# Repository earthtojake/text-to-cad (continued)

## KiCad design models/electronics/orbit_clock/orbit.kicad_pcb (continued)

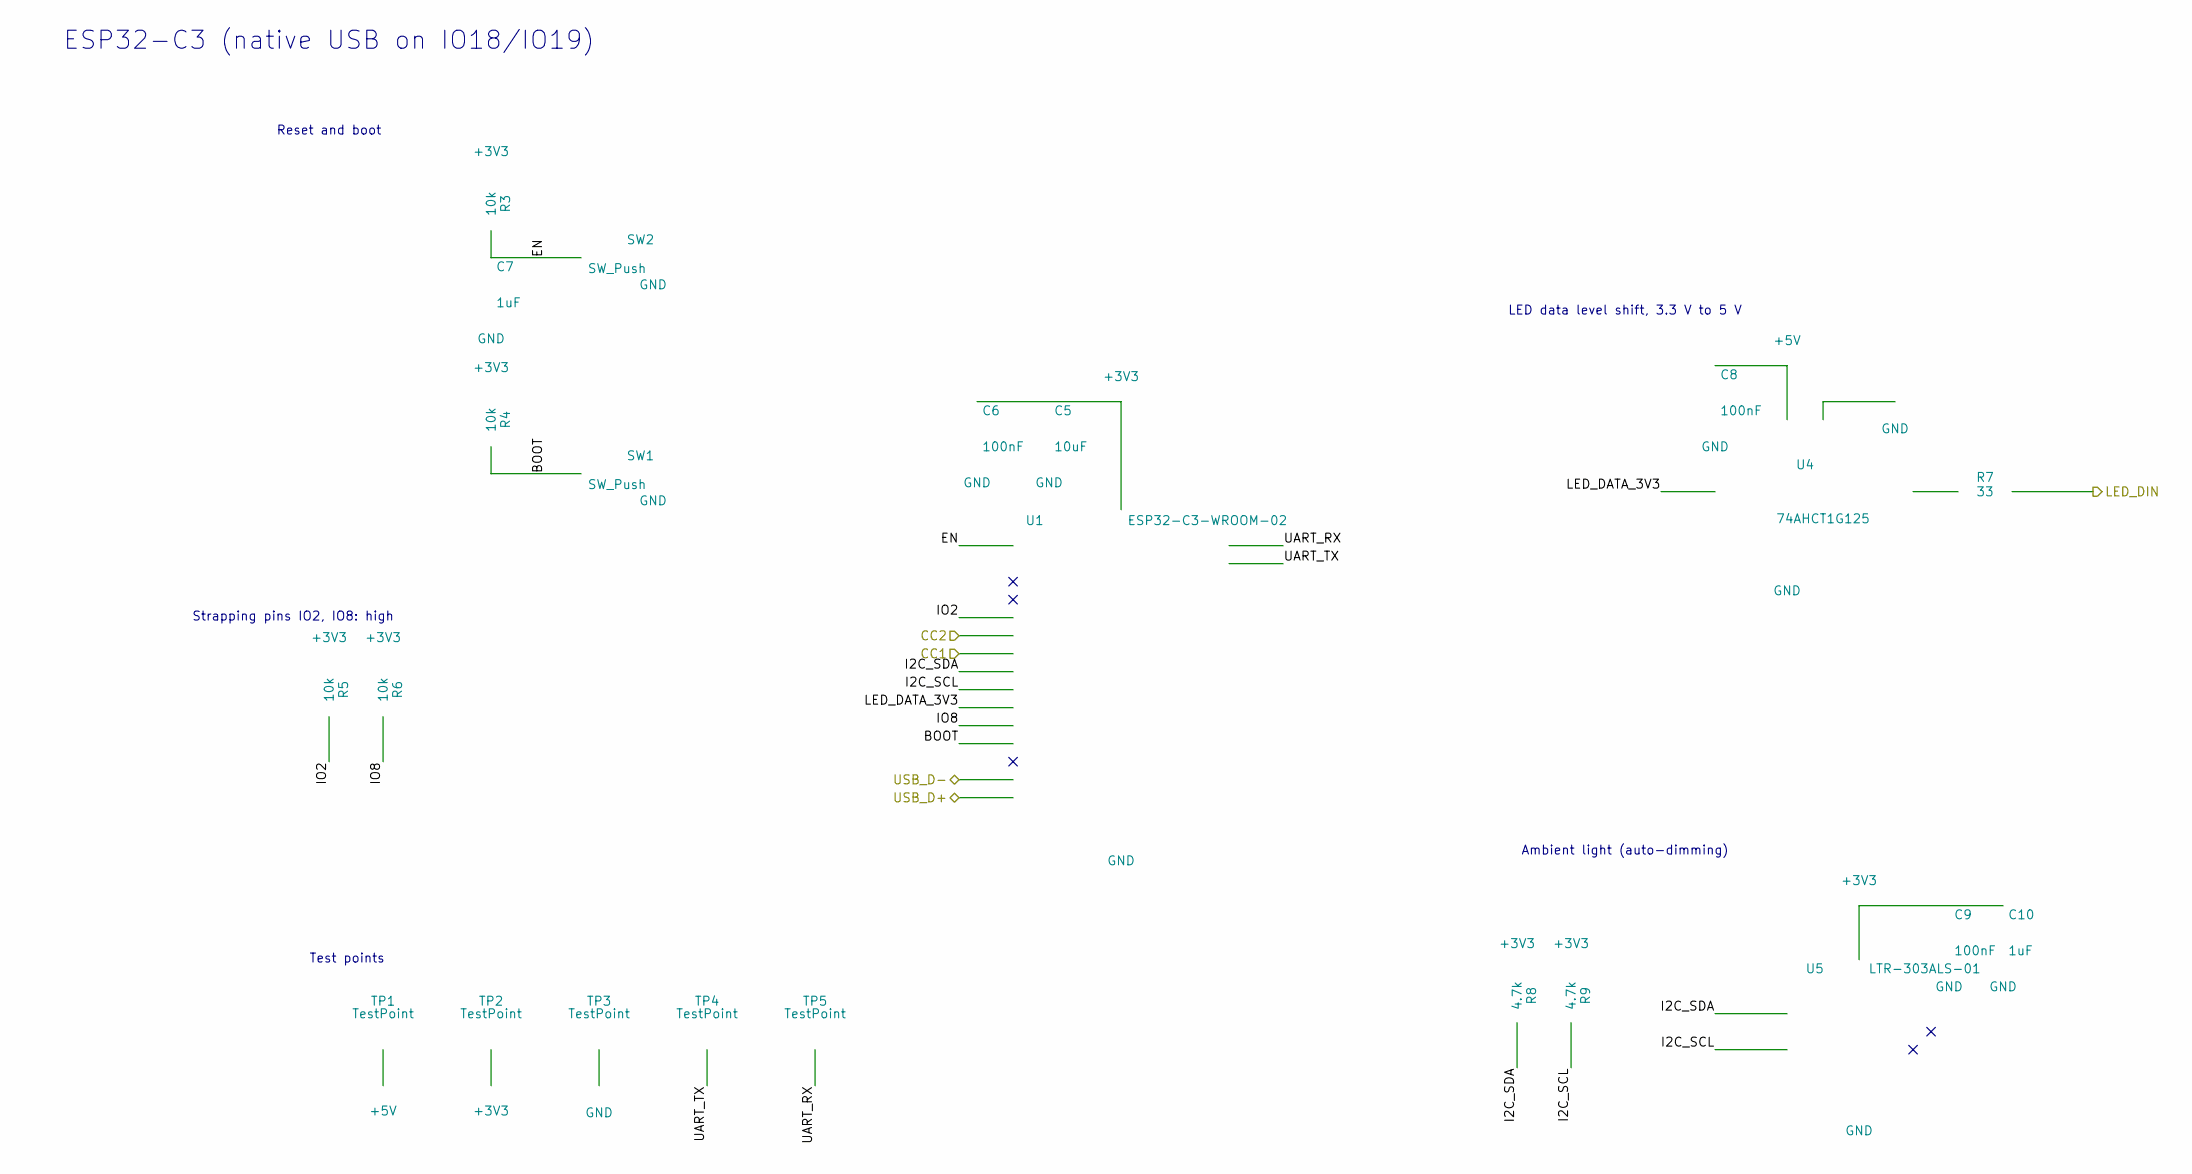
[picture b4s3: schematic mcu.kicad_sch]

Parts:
C5: 10uF; C_0805_2012Metric; MPN CL21A106KAYNNNE
C6, C8, C9: 100nF; C_0603_1608Metric; MPN CL10B104KB8NNNC
C7, C10: 1uF; C_0603_1608Metric; MPN CL10A105KB8NNNC
R3, R4, R5, R6: 10k; R_0603_1608Metric; MPN RC0603FR-0710KL
R7: 33; R_0603_1608Metric; MPN RC0603FR-0733RL
R8, R9: 4.7k; R_0603_1608Metric; MPN RC0603FR-074K7L
SW1, SW2: SW_Push; SW_SPST_TL3342; MPN TL3342F160QG
TP1, TP2, TP3, TP4, TP5: TestPoint; TestPoint_Pad_D1.5mm
U1: ESP32-C3-WROOM-02; MPN ESP32-C3-WROOM-02-N4
U4: 74AHCT1G125; SOT-23-5; MPN SN74AHCT1G125DBVR
U5: LTR-303ALS-01; Lite-On_LTR-303ALS-01; MPN LTR-303ALS-01

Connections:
+3V3: C5.1, C6.1, C9.1, C10.1, R3.1, R4.1, R5.1, R6.1, R8.1, R9.1, TP2.1 (1_1), U1.1 (3V3), U5.1 (VDD); also elsewhere on the board
+5V: C8.1, TP1.1 (1_1), U4.5 (VCC); also elsewhere on the board
/MCU/BOOT: R4.2, SW1.1, U1.8 (IO9)
/MCU/CC1: U1.3 (IO4); also elsewhere on the board
/MCU/CC2: U1.15 (IO3); also elsewhere on the board
/MCU/EN: C7.1, R3.2, SW2.1, U1.2 (EN)
/MCU/I2C_SCL: R9.2, U1.5 (IO6), U5.4 (SCL)
/MCU/I2C_SDA: R8.2, U1.4 (IO5), U5.6 (SDA)
/MCU/IO2: R5.2, U1.16 (IO2)
/MCU/IO8: R6.2, U1.7 (IO8)
/MCU/LED_DATA_3V3: U1.6 (IO7), U4.2
/MCU/LED_DIN: R7.2; also elsewhere on the board
/MCU/UART_RX: TP5.1 (1_1), U1.11 (IO20/RXD)
/MCU/UART_TX: TP4.1 (1_1), U1.12 (IO21/TXD)
/Power/USB_D+: U1.14 (IO19); also elsewhere on the board
/Power/USB_D-: U1.13 (IO18); also elsewhere on the board
GND: C5.2, C6.2, C7.2, C8.2, C9.2, C10.2, SW1.2, SW2.2, TP3.1 (1_1), U1.9 (GND), U1.19 (GND), U4.1, U4.3 (GND), U5.3 (GND); also elsewhere on the board
unnamed: R7.1, U4.4

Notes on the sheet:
ESP32-C3 (native USB on IO18/IO19)
Ambient light (auto-dimming)
LED data level shift, 3.3 V to 5 V
Strapping pins IO2, IO8: high
Reset and boot
Test points

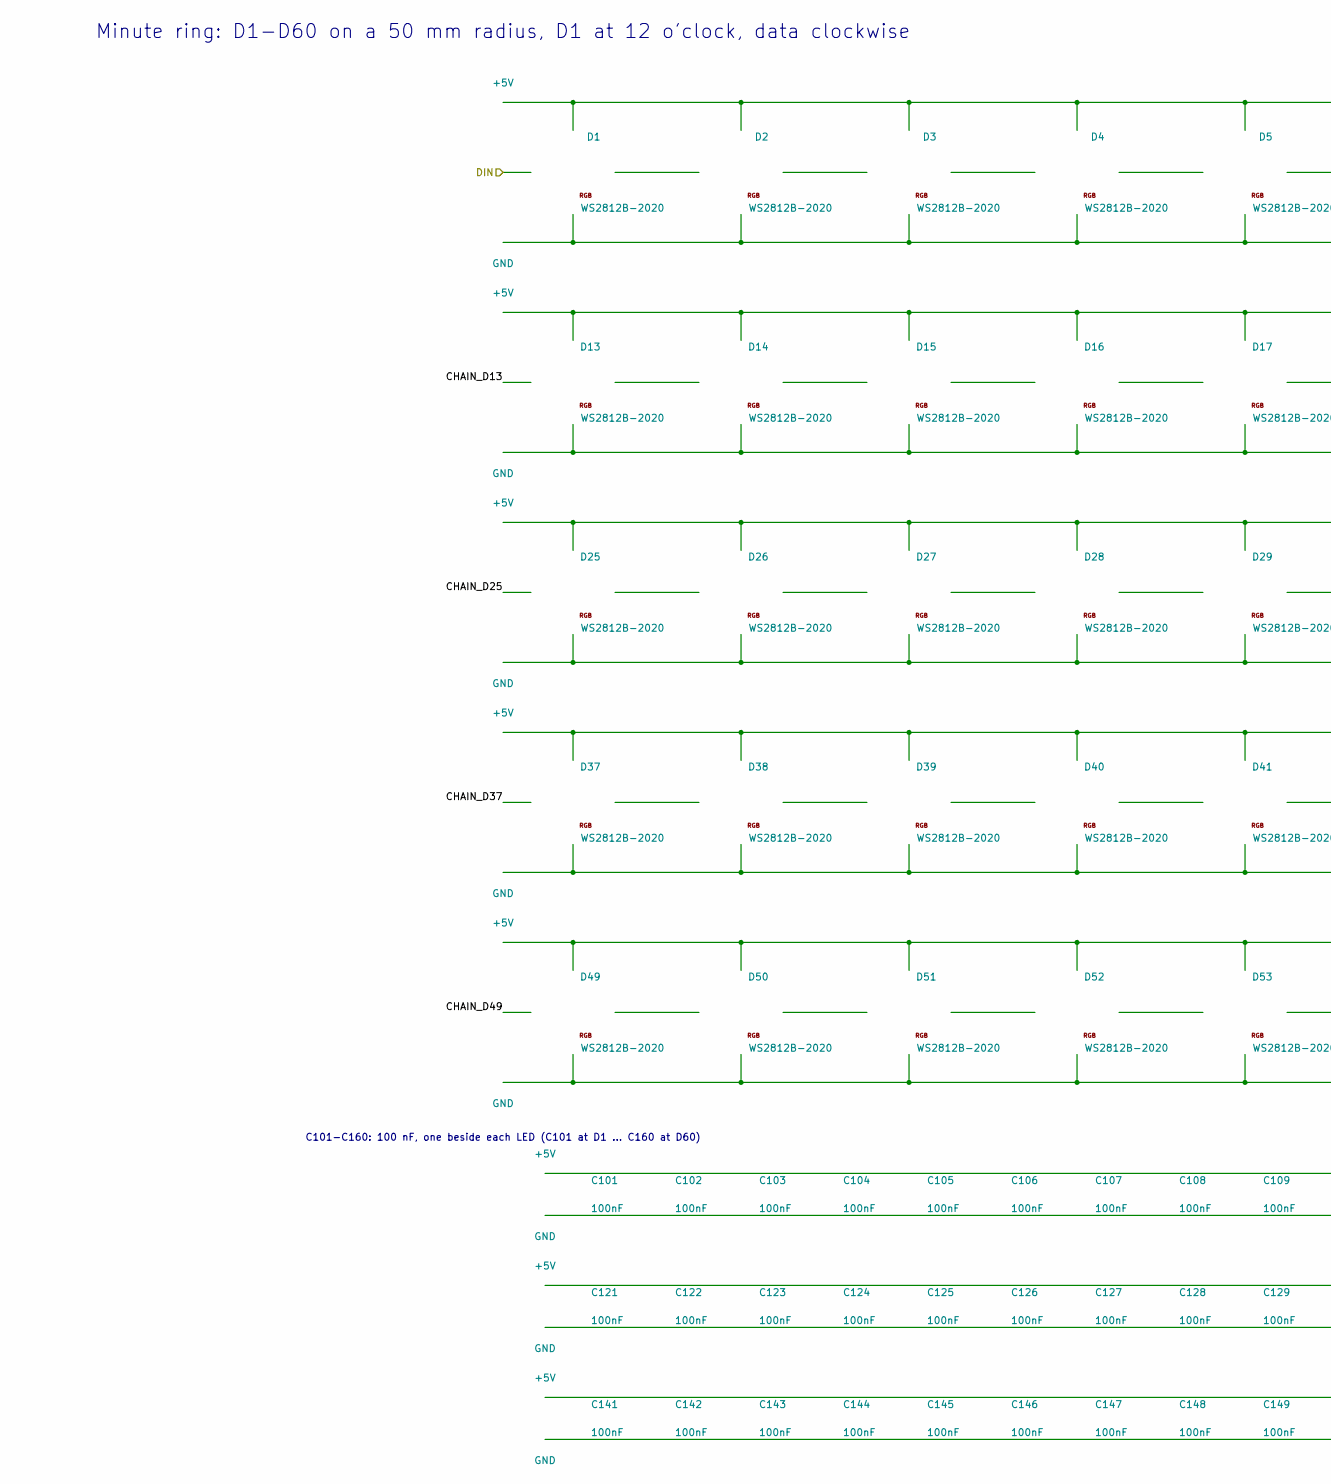
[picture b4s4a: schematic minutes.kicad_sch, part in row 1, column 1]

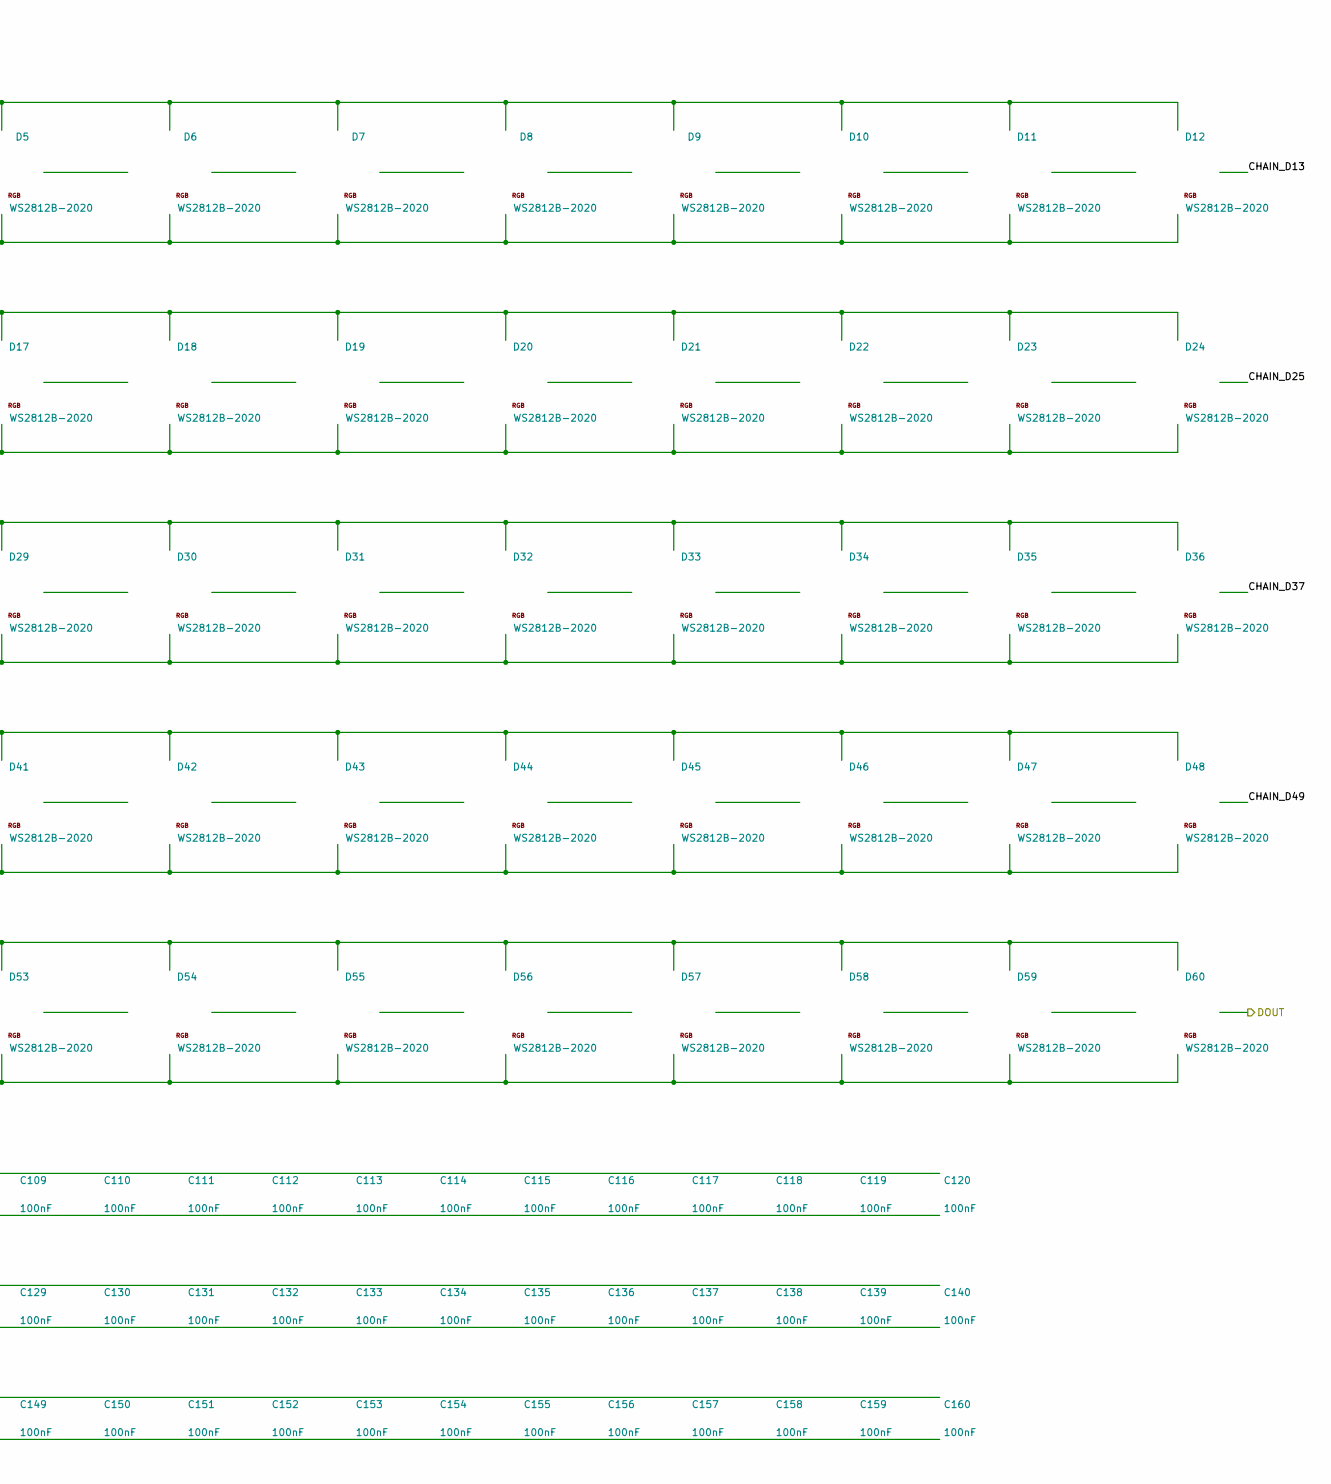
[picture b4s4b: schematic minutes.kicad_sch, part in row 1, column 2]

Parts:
C101, C102, C103, C104, C105, C106, C107, C108, C109, C110, C111, C112, C113, C114, C115, C116, C117, C118, C119, C120, C121, C122, C123, C124, C125, C126, C127, C128, C129, C130, C131, C132, C133, C134, C135, C136, C137, C138, C139, C140, C141, C142, C143, C144, C145, C146, C147, C148, C149, C150, C151, C152, C153, C154, C155, C156, C157, C158, C159, C160: 100nF; C_0603_1608Metric; MPN CL10B104KB8NNNC
D1, D2, D3, D4, D5, D6, D7, D8, D9, D10, D11, D12, D13, D14, D15, D16, D17, D18, D19, D20, D21, D22, D23, D24, D25, D26, D27, D28, D29, D30, D31, D32, D33, D34, D35, D36, D37, D38, D39, D40, D41, D42, D43, D44, D45, D46, D47, D48, D49, D50, D51, D52, D53, D54, D55, D56, D57, D58, D59, D60: WS2812B-2020; LED_WS2812B-2020_PLCC4_2.0x2.0mm; MPN WS2812B-2020

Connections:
+5V: C101.1, C102.1, C103.1, C104.1, C105.1, C106.1, C107.1, C108.1, C109.1, C110.1, C111.1, C112.1, C113.1, C114.1, C115.1, C116.1, C117.1, C118.1, C119.1, C120.1, C121.1, C122.1, C123.1, C124.1, C125.1, C126.1, C127.1, C128.1, C129.1, C130.1, C131.1, C132.1, C133.1, C134.1, C135.1, C136.1, C137.1, C138.1, C139.1, C140.1, C141.1, C142.1, C143.1, C144.1, C145.1, C146.1, C147.1, C148.1, C149.1, C150.1, C151.1, C152.1, C153.1, C154.1, C155.1, C156.1, C157.1, C158.1, C159.1, C160.1, D1.4 (VDD), D2.4 (VDD), D3.4 (VDD), D4.4 (VDD), D5.4 (VDD), D6.4 (VDD), D7.4 (VDD), D8.4 (VDD), D9.4 (VDD), D10.4 (VDD), D11.4 (VDD), D12.4 (VDD), D13.4 (VDD), D14.4 (VDD), D15.4 (VDD), D16.4 (VDD), D17.4 (VDD), D18.4 (VDD), D19.4 (VDD), D20.4 (VDD), D21.4 (VDD), D22.4 (VDD), D23.4 (VDD), D24.4 (VDD), D25.4 (VDD), D26.4 (VDD), D27.4 (VDD), D28.4 (VDD), D29.4 (VDD), D30.4 (VDD), D31.4 (VDD), D32.4 (VDD), D33.4 (VDD), D34.4 (VDD), D35.4 (VDD), D36.4 (VDD), D37.4 (VDD), D38.4 (VDD), D39.4 (VDD), D40.4 (VDD), D41.4 (VDD), D42.4 (VDD), D43.4 (VDD), D44.4 (VDD), D45.4 (VDD), D46.4 (VDD), D47.4 (VDD), D48.4 (VDD), D49.4 (VDD), D50.4 (VDD), D51.4 (VDD), D52.4 (VDD), D53.4 (VDD), D54.4 (VDD), D55.4 (VDD), D56.4 (VDD), D57.4 (VDD), D58.4 (VDD), D59.4 (VDD), D60.4 (VDD); also elsewhere on the board
/Hour ring/DIN: D60.1 (DOUT); also elsewhere on the board
/MCU/LED_DIN: D1.3 (DIN); also elsewhere on the board
/Minute ring/CHAIN_D13: D12.1 (DOUT), D13.3 (DIN)
/Minute ring/CHAIN_D25: D24.1 (DOUT), D25.3 (DIN)
/Minute ring/CHAIN_D37: D36.1 (DOUT), D37.3 (DIN)
/Minute ring/CHAIN_D49: D48.1 (DOUT), D49.3 (DIN)
GND: C101.2, C102.2, C103.2, C104.2, C105.2, C106.2, C107.2, C108.2, C109.2, C110.2, C111.2, C112.2, C113.2, C114.2, C115.2, C116.2, C117.2, C118.2, C119.2, C120.2, C121.2, C122.2, C123.2, C124.2, C125.2, C126.2, C127.2, C128.2, C129.2, C130.2, C131.2, C132.2, C133.2, C134.2, C135.2, C136.2, C137.2, C138.2, C139.2, C140.2, C141.2, C142.2, C143.2, C144.2, C145.2, C146.2, C147.2, C148.2, C149.2, C150.2, C151.2, C152.2, C153.2, C154.2, C155.2, C156.2, C157.2, C158.2, C159.2, C160.2, D1.2 (VSS), D2.2 (VSS), D3.2 (VSS), D4.2 (VSS), D5.2 (VSS), D6.2 (VSS), D7.2 (VSS), D8.2 (VSS), D9.2 (VSS), D10.2 (VSS), D11.2 (VSS), D12.2 (VSS), D13.2 (VSS), D14.2 (VSS), D15.2 (VSS), D16.2 (VSS), D17.2 (VSS), D18.2 (VSS), D19.2 (VSS), D20.2 (VSS), D21.2 (VSS), D22.2 (VSS), D23.2 (VSS), D24.2 (VSS), D25.2 (VSS), D26.2 (VSS), D27.2 (VSS), D28.2 (VSS), D29.2 (VSS), D30.2 (VSS), D31.2 (VSS), D32.2 (VSS), D33.2 (VSS), D34.2 (VSS), D35.2 (VSS), D36.2 (VSS), D37.2 (VSS), D38.2 (VSS), D39.2 (VSS), D40.2 (VSS), D41.2 (VSS), D42.2 (VSS), D43.2 (VSS), D44.2 (VSS), D45.2 (VSS), D46.2 (VSS), D47.2 (VSS), D48.2 (VSS), D49.2 (VSS), D50.2 (VSS), D51.2 (VSS), D52.2 (VSS), D53.2 (VSS), D54.2 (VSS), D55.2 (VSS), D56.2 (VSS), D57.2 (VSS), D58.2 (VSS), D59.2 (VSS), D60.2 (VSS); also elsewhere on the board
unnamed: D1.1 (DOUT), D2.3 (DIN)
unnamed: D2.1 (DOUT), D3.3 (DIN)
unnamed: D3.1 (DOUT), D4.3 (DIN)
unnamed: D4.1 (DOUT), D5.3 (DIN)
unnamed: D5.1 (DOUT), D6.3 (DIN)
unnamed: D6.1 (DOUT), D7.3 (DIN)
unnamed: D7.1 (DOUT), D8.3 (DIN)
unnamed: D8.1 (DOUT), D9.3 (DIN)
unnamed: D9.1 (DOUT), D10.3 (DIN)
unnamed: D10.1 (DOUT), D11.3 (DIN)
unnamed: D11.1 (DOUT), D12.3 (DIN)
unnamed: D13.1 (DOUT), D14.3 (DIN)
unnamed: D14.1 (DOUT), D15.3 (DIN)
unnamed: D15.1 (DOUT), D16.3 (DIN)
unnamed: D16.1 (DOUT), D17.3 (DIN)
unnamed: D17.1 (DOUT), D18.3 (DIN)
unnamed: D18.1 (DOUT), D19.3 (DIN)
unnamed: D19.1 (DOUT), D20.3 (DIN)
unnamed: D20.1 (DOUT), D21.3 (DIN)
unnamed: D21.1 (DOUT), D22.3 (DIN)
unnamed: D22.1 (DOUT), D23.3 (DIN)
unnamed: D23.1 (DOUT), D24.3 (DIN)
unnamed: D25.1 (DOUT), D26.3 (DIN)
unnamed: D26.1 (DOUT), D27.3 (DIN)
unnamed: D27.1 (DOUT), D28.3 (DIN)
unnamed: D28.1 (DOUT), D29.3 (DIN)
unnamed: D29.1 (DOUT), D30.3 (DIN)
unnamed: D30.1 (DOUT), D31.3 (DIN)
unnamed: D31.1 (DOUT), D32.3 (DIN)
unnamed: D32.1 (DOUT), D33.3 (DIN)
unnamed: D33.1 (DOUT), D34.3 (DIN)
unnamed: D34.1 (DOUT), D35.3 (DIN)
unnamed: D35.1 (DOUT), D36.3 (DIN)
unnamed: D37.1 (DOUT), D38.3 (DIN)
unnamed: D38.1 (DOUT), D39.3 (DIN)
unnamed: D39.1 (DOUT), D40.3 (DIN)
unnamed: D40.1 (DOUT), D41.3 (DIN)
unnamed: D41.1 (DOUT), D42.3 (DIN)
unnamed: D42.1 (DOUT), D43.3 (DIN)
unnamed: D43.1 (DOUT), D44.3 (DIN)
unnamed: D44.1 (DOUT), D45.3 (DIN)
unnamed: D45.1 (DOUT), D46.3 (DIN)
unnamed: D46.1 (DOUT), D47.3 (DIN)
unnamed: D47.1 (DOUT), D48.3 (DIN)
unnamed: D49.1 (DOUT), D50.3 (DIN)
unnamed: D50.1 (DOUT), D51.3 (DIN)
unnamed: D51.1 (DOUT), D52.3 (DIN)
unnamed: D52.1 (DOUT), D53.3 (DIN)
unnamed: D53.1 (DOUT), D54.3 (DIN)
unnamed: D54.1 (DOUT), D55.3 (DIN)
unnamed: D55.1 (DOUT), D56.3 (DIN)
unnamed: D56.1 (DOUT), D57.3 (DIN)
unnamed: D57.1 (DOUT), D58.3 (DIN)
unnamed: D58.1 (DOUT), D59.3 (DIN)
unnamed: D59.1 (DOUT), D60.3 (DIN)

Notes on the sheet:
Minute ring: D1-D60 on a 50 mm radius, D1 at 12 o'clock, data clockwise
C101-C160: 100 nF, one beside each LED (C101 at D1 ... C160 at D60)

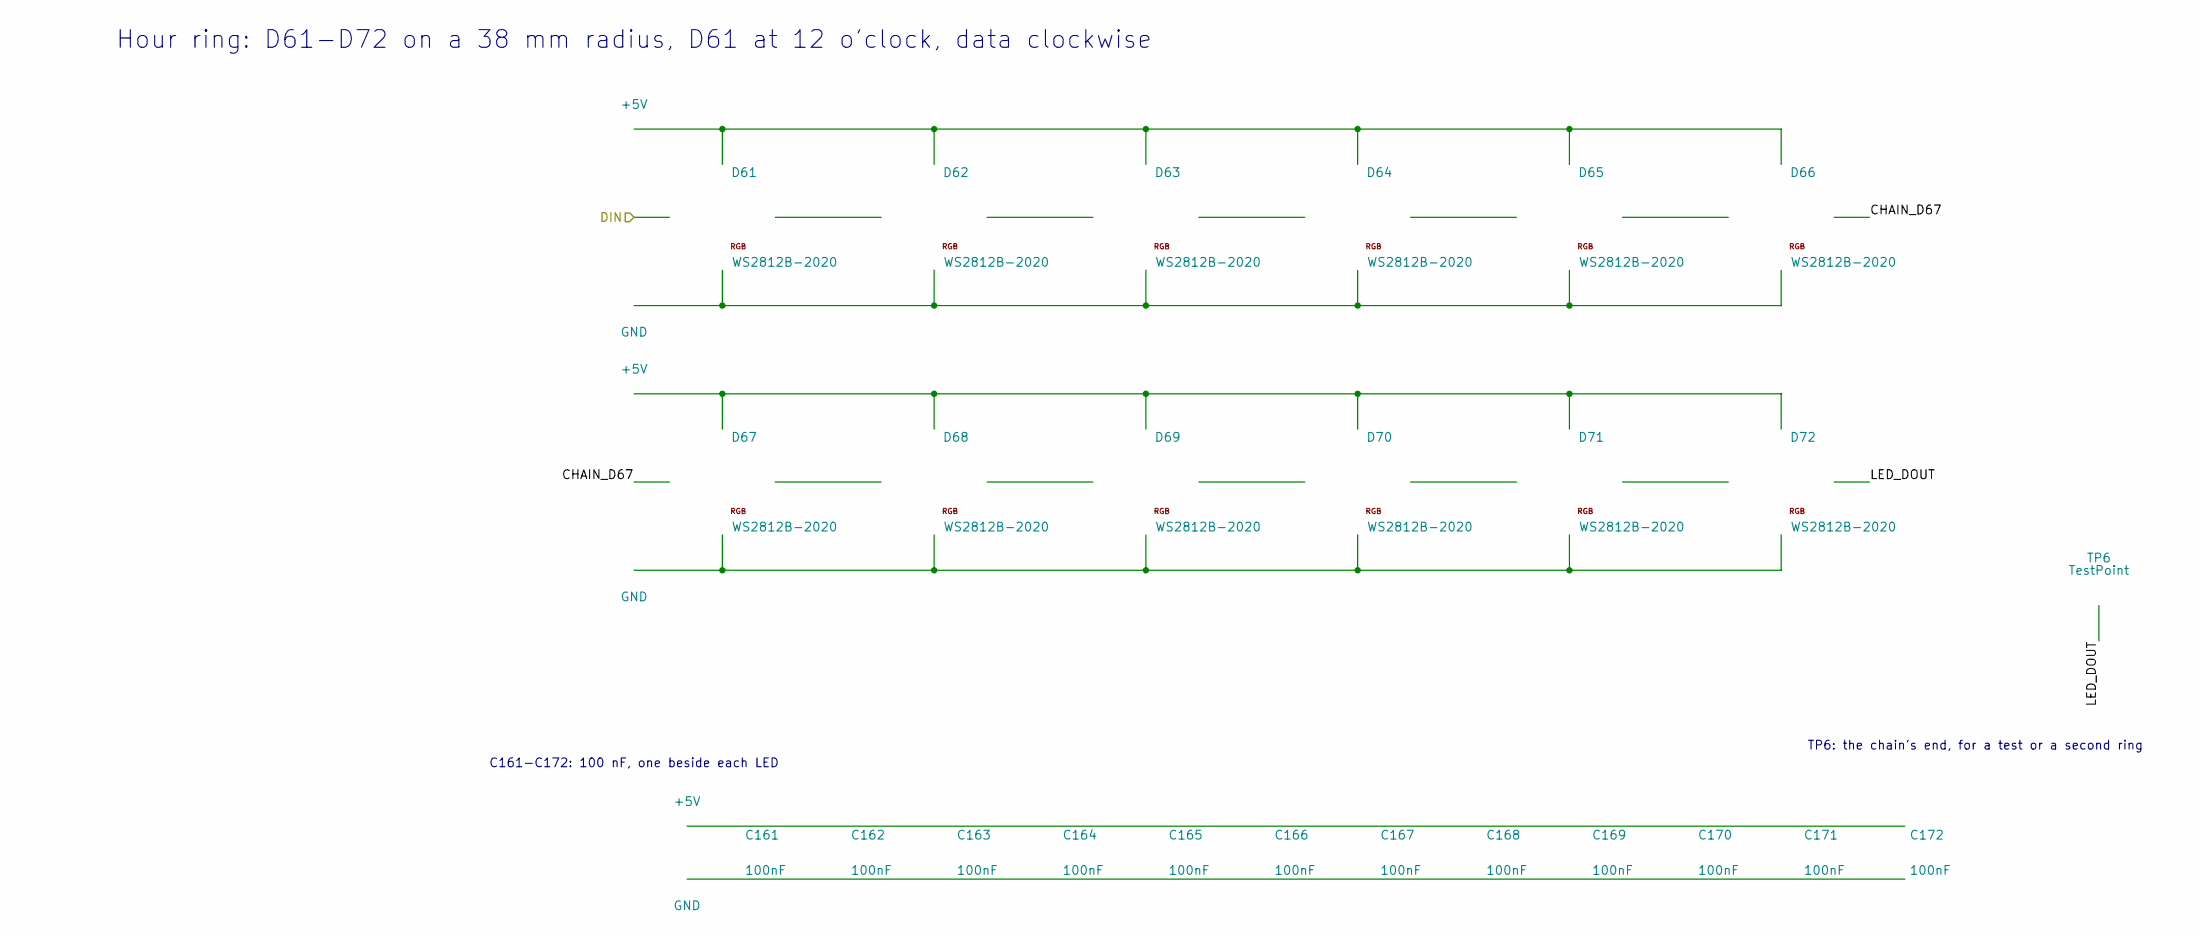
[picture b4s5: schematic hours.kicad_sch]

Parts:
C161, C162, C163, C164, C165, C166, C167, C168, C169, C170, C171, C172: 100nF; C_0603_1608Metric; MPN CL10B104KB8NNNC
D61, D62, D63, D64, D65, D66, D67, D68, D69, D70, D71, D72: WS2812B-2020; LED_WS2812B-2020_PLCC4_2.0x2.0mm; MPN WS2812B-2020
TP6: TestPoint; TestPoint_Pad_D1.5mm

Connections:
+5V: C161.1, C162.1, C163.1, C164.1, C165.1, C166.1, C167.1, C168.1, C169.1, C170.1, C171.1, C172.1, D61.4 (VDD), D62.4 (VDD), D63.4 (VDD), D64.4 (VDD), D65.4 (VDD), D66.4 (VDD), D67.4 (VDD), D68.4 (VDD), D69.4 (VDD), D70.4 (VDD), D71.4 (VDD), D72.4 (VDD); also elsewhere on the board
/Hour ring/CHAIN_D67: D66.1 (DOUT), D67.3 (DIN)
/Hour ring/DIN: D61.3 (DIN); also elsewhere on the board
/Hour ring/LED_DOUT: D72.1 (DOUT), TP6.1 (1_1)
GND: C161.2, C162.2, C163.2, C164.2, C165.2, C166.2, C167.2, C168.2, C169.2, C170.2, C171.2, C172.2, D61.2 (VSS), D62.2 (VSS), D63.2 (VSS), D64.2 (VSS), D65.2 (VSS), D66.2 (VSS), D67.2 (VSS), D68.2 (VSS), D69.2 (VSS), D70.2 (VSS), D71.2 (VSS), D72.2 (VSS); also elsewhere on the board
unnamed: D61.1 (DOUT), D62.3 (DIN)
unnamed: D62.1 (DOUT), D63.3 (DIN)
unnamed: D63.1 (DOUT), D64.3 (DIN)
unnamed: D64.1 (DOUT), D65.3 (DIN)
unnamed: D65.1 (DOUT), D66.3 (DIN)
unnamed: D67.1 (DOUT), D68.3 (DIN)
unnamed: D68.1 (DOUT), D69.3 (DIN)
unnamed: D69.1 (DOUT), D70.3 (DIN)
unnamed: D70.1 (DOUT), D71.3 (DIN)
unnamed: D71.1 (DOUT), D72.3 (DIN)

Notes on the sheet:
Hour ring: D61-D72 on a 38 mm radius, D61 at 12 o'clock, data clockwise
TP6: the chain's end, for a test or a second ring
C161-C172: 100 nF, one beside each LED

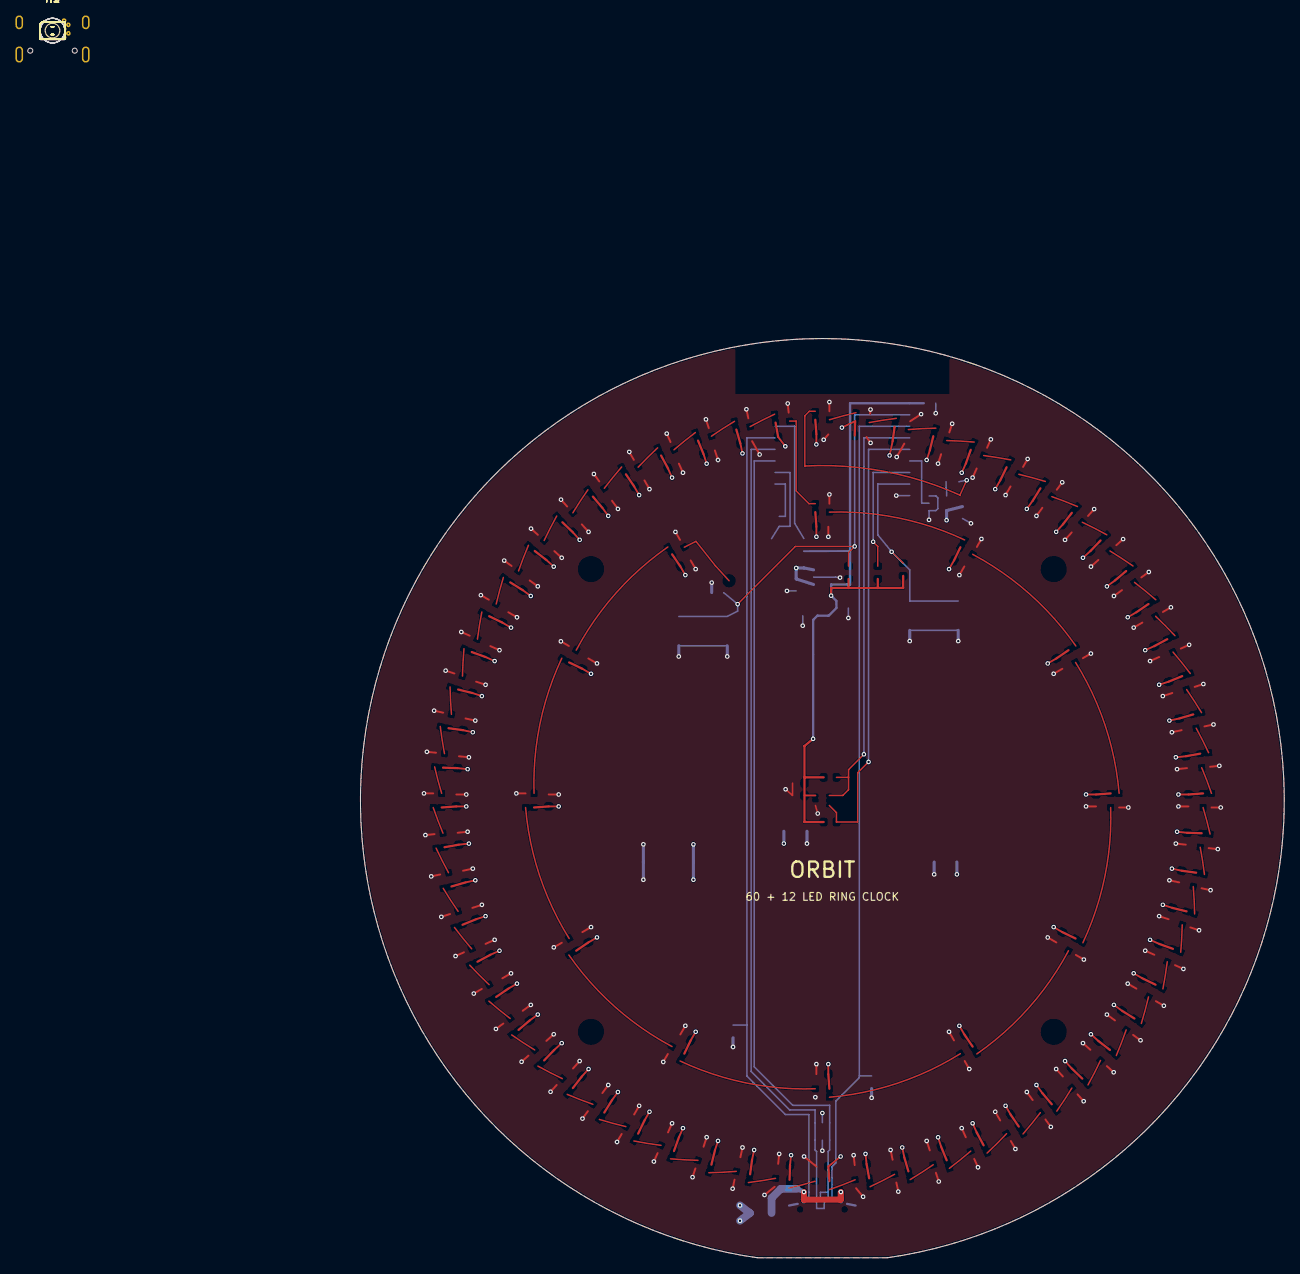
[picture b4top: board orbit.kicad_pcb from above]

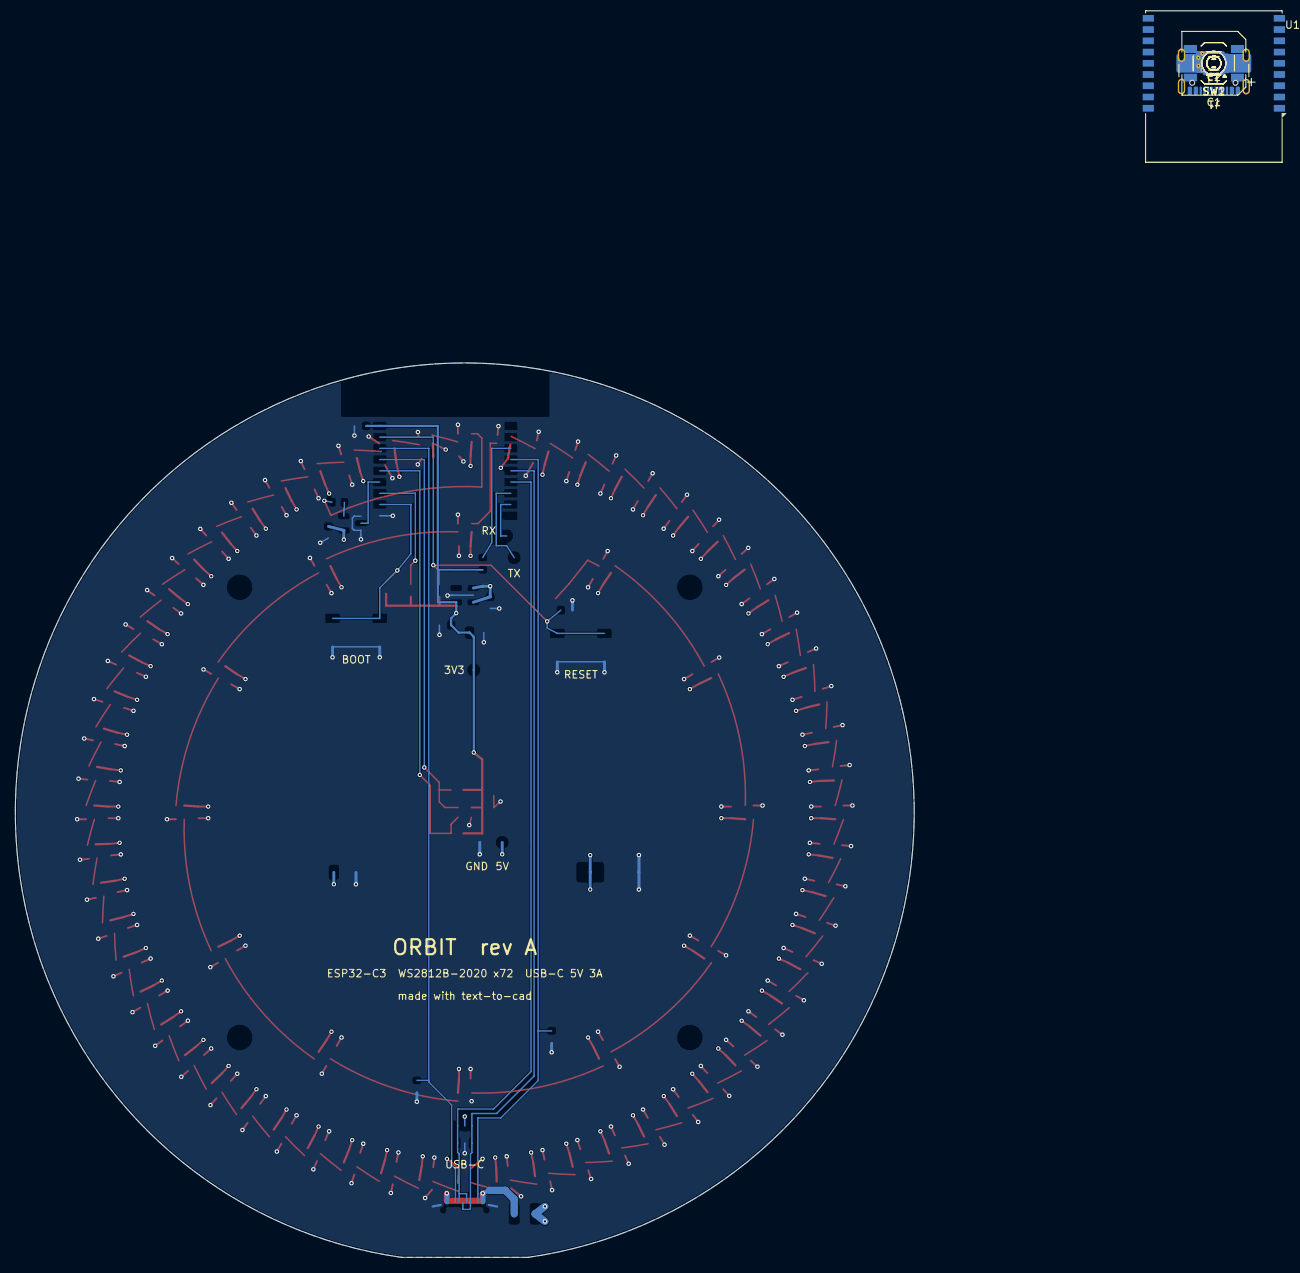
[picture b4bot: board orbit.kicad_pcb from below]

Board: 4 copper layers, 120.0 x 119.4 mm, 182 parts (25 on the bottom side), 91 nets.

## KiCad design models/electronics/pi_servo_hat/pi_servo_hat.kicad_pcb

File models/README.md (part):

# Models

The corpus of models built with text-to-cad: plain files, one flat level of
self-contained projects, built by running their scripts; nothing installs it.
Automated tests never read, build or import anything here: they make their own
fixtures in fresh temporary directories. The manual-validation cases live in
[tests/](tests/README.md).

Each project has one layout, the cad skill's: its sources in `src/` (shared modules in
`src/lib/`), each model a `@model` function its script calls under `if __name__ ==
"__main__":`. A run writes nothing: it builds the model in the engine and prints its
document's `id:` and page (`view:`), which every later run updates. A file is written
on request, `cad model export <id> STEP/<name>.step`, into the project's root-level
`STEP/`, `STL/`, `GLB/`, `3MF/` or `DXF/`, which each project's `.gitignore` keeps out
of Git. `juno` and `lyra` carry an authored URDF and SRDF beside `src/`; the link meshes
they reference are written by each project's `exports.py` (`3MF/<link>.3mf`), so run it
before loading either URDF.

[`mujoco`](mujoco/README.md) holds two sample projects from makers' CAD, not robots of ours: it fetches two makers' raw
CAD (The Robot Studio's SO-101 and Trossen's WidowX AI assembly STEPs, pinned in
`src/sources.py`), turns each into an articulated model and exports it as MJCF and URDF,
then compares the result with Google's hand-made MuJoCo Menagerie model and the maker's own URDF.
Nothing it fetches or writes is committed: `python src/fetch.py` downloads the sources into
ignored folders.

Every model of the old corpus is ported, but for tendon_hand's 56 review models (reviews
and clearance studies on frozen STEP snapshots, not the hand: dropped, in Git history) and
`tom`, the arm, which lives in its own repository. One file is no model:
`tests/unported/joint_playground/joint_playground.urdf`, named nowhere, kept with its README.

**Where does a new model go?** A standalone part that is one script goes in
`examples/src/` (a `@model`), an assembly gets a group in `assemblies/`
(`src/<group>/`), and a 2D drawing a script in `drawings/src/`, its DXF added to
`drawings/src/exports.py`. A model that needs helper modules, several scripts or notes
of its own gets a project of its own here. A KiCad board is no model: it lives one folder each in
`electronics/`, with the pcb skill's checks of it as a script (`cad run check_<board>.py`). Four are boards alone
(`blinky`, `usb_uart`, `servo_power`, `pi_servo_hat`): no script makes them, so their native files (`.kicad_pcb`,
`.kicad_pro`, `.kicad_dru`, `fp-lib-table`) are the source, committed. Four are ECAD samples, each board made by
its scripts: the KiCad files those scripts write (the board, the schematic's sheets, the project file and its rules, the
project's own libraries and their tables) are build output, gitignored and made again by the sample's one command,
`cad run build.py`, which its README puts first; build before opening the board in the viewer or in KiCad, or
running anything that reads it. A KiCad file beside such a build that no script writes stays source (macropad's
library tables, eurorack_lfo's project file), and `tests/python/global/test_generated_kicad_files_untracked.py`
holds both lists. Three have the CAD built around the board in the cad skill's layout beside it (`src/`), read from
the board file, and the scripts that make the board (`scripts/`): [`macropad`](electronics/macropad/README.md),
[`eurorack_lfo`](electronics/eurorack_lfo/README.md) and [`orbit_clock`](electronics/orbit_clock/README.md). The
fourth, [`pinball`](electronics/pinball/README.md), runs the other way: the design model (`src/`) is the source of
the board's outline, holes and art, and the board's scripts, build and checks live in `board/`.

Commit sources (`*.py`, `*.urdf`, `*.srdf`, the JSON a body reads, the KiCad files no script writes, docs); never
what a run, a build or an export writes (Git holds code, never CAD or mesh files: no STEP, STL, GLB, 3MF, DXF or
XBF, no KiCad file a sample's scripts write, and no `.blend`, which a render's bpy script makes), review media
(`.gitignore` keeps images and video out of this tree) or runtime debris. One project renders with Blender:
`orbit_clock`'s `render.py`, a bpy script `cad run` runs, writes its stills into the project's gitignored `RENDERS/`.

Two rules reach a new project from outside this folder, and the policy suite holds both; run it
(`scripts/test/test-global.sh`, under a minute) before the first push. A script named `build.py` under `models/` is
a KiCad sample's build and nothing else: `test_generated_kicad_files_untracked.py` asks every folder that tracks
one which KiCad files it writes, so a script that builds anything else takes another name. And every tracked path
is one a CI rule names (`scripts/github-workflows/select_checks.py`): a file under `models/` is, a new file at the
repository's root is not until a rule there names it, so a project's notes go in its own folder.

## The files the corpus writes

Most models write nothing. A few keep files on purpose, as examples of each way a
project delivers them and because something outside the model reads them:

| Project | Files | How | Why |
| --- | --- | --- | --- |
| `assemblies` (`planetary_gear_assembly`) | `apps/docs/public/hero/planetary.glb` | `cad <type> export` of its document, by hand (`apps/docs/README.md`) | the docs site's hero plays its `meshCycle` clip; a hand step, its clip's playback checked before the GLB is committed (no CI job reads the model) |
| `examples` (`mounting_plate`, `spur_gear_blank`) | `STL/`, `3MF/`, `GLB/<name>.*` | `@stl`, `@threemf`, `@glb` on the model | the example of declared files: a print part whose files every run writes |
| `branding` (the three logos) | `STEP/logo_*.step` | `src/exports.py` | the STEP deliverable, kept current by an `exports.py` |
| `drawings` (all eight) | `DXF/<name>.dxf` | `src/exports.py` | the DXF deliverables, flat patterns among them; a drawing exists for its DXF |
| `juno`, `lyra` (every link model) | `3MF/<link>.3mf` | `src/exports.py` | the URDFs reference them |
| `examples` (`electronics_enclosure_base_drawing`) | `PDF/electronics_enclosure_base_drawing.pdf` | `@eng_drawing` | an engineering drawing is its PDF |
| `examples` (`electronics_enclosure_base_import`) | `STEP/electronics_enclosure_base.step`, `STEP/basic_shape_mating_test_fixture.step` | `cad.model.export(model, path)` in the script's `__main__` | the two import models read them back; made on the spot, so no STEP is committed |
| `radial` | `XBF/radial.xbf` | `@xbf` | the slow model's result kept across runs and engine restarts: a cold build takes most of an hour; every body replays, and a no-op takes the file (0.2 s) instead of sampling the running motion again (5.6 s without it) |
| `electronics` (`macropad`, `eurorack_lfo`, `orbit_clock`, `pinball`) | the KiCad project: the board, the schematic's sheets, the project file and rules, the project's libraries and their tables (each sample's `.gitignore` names them) | `cad run build.py` (`pinball`: `board/build.py`), the board's scripts in order | the board is made by its scripts, which are its source; ERC, DRC, the checks, the viewer, KiCad and the CAD scripts read it, so build before any of them |
| `electronics` (`macropad`, `eurorack_lfo`, `orbit_clock`, `pinball`) | `macropad.3dshapes/`, `3dmodels/`, `orbit.3dshapes/`, `board/pinball.3dshapes/` (a STEP each) | `@step` on each part model (`src/vendor_parts.py`, `src/footprint_models.py`, `src/part_models.py`, `board/scripts/part_models.py`) | the footprints KiCad's library has no model for name them (`${KIPRJMOD}/...`): the board's 3D view and its STEP and GLB exports read them, so run the script before either |
| `electronics` (`macropad`, `eurorack_lfo`, `orbit_clock`) | `3MF/`, `STEP/`, `GLB/`, `DXF/` | `src/exports.py` | the printed parts in their print orientation, the panel's cut and art DXFs, the assemblies' STEP and GLB (the GLB carries the explode) |

## Build and snapshot

From a model's `src/` folder, with the engine's environment (the library on the path):

```
python SCRIPT.py                         # the models its __main__ calls: each prints id: and view:
cad model snapshot "$ID" OUT.png            # drawn by OCCT
cad model export "$ID" GLB/NAME.glb         # a file of it, on request
```

A model script is Python and takes no options: running it asks the engine to build each
model its `__main__` calls, in the script's warm worker (the engine starts on demand;
`cad stop` stops it), so a second run of an unchanged model replays it from memory.
A script's models count as one run of the memo's last four, however many it builds, so a
robot and its links replay together. Nothing is written beside a model: no sidecar, no
cache.

## The port

The migration a user makes ([the migration guide](../docs/migrations/migrating-0.7-to-0.8.md)),
and nothing more:

- `from cadgen import step` -> `from cad import model` (`from cadgen import model` in 0.8; and
  `memo`, `paint`, `read_step`, `read_xbf`, `read_mesh`, `export`); 0.7's build123d proxy ->
  `import build123d as bd`; `cad.ap242` for the mechanism and `cad.gltf` for a GLB's animations.
- `@step(out=...)` -> `@model`, and nothing else, but where the table above keeps a file.
  Every script calls its models under `__main__`; a module of `@memo` stages or plain
  helpers calls nothing there.
- `materials=` finishes -> native `bd_materials.FinishedMaterial` values with
  explicit `threejs_materials.PbrProperties`, set on the parts (`part.material = ...`) and
  `paint(part, faces, material)` for a face finish; colours as sRGB hex. Native
  material assignment applies its colour: restore a part’s authored colour after it
  where the palette supplies the colour. Physical properties come from `bd_materials`
  factories; `RangeMaterial` names the project-specific materials absent from them.
- Mates (`AssemblyHelper` frames, `KINEMATICS` revolute/fastened) -> build123d joints
  (`RigidJoint`, `RevoluteJoint`, ...) placed with `connect_to`, or paired by label where
  `connect_to` cannot place a part in a nested assembly. The as-built pose is where the
  joints connect the parts. A coupling, named after the pair it is written as
  (`gear_pair`, `rack_and_pinion_pair`, `screw_pair`), is a real mechanical relation and a
  constraint: the gear trains (the moonwatch's `running` and `chrono`, the qdd, planetary
  and radial `drive`), the mars rover's differential (`rocker_split`) and the tendon
  hand's curls. Poses are `mechanism_state(...)`.
- Animation (`animation=` JavaScript, `cadgen.clip`) -> two layers. The mechanism's own
  motion (a gait, a door, an engine running) is a `configuration_sequence`, kept in the
  document. A showcase (an explode, a teardown, a reveal, a part hidden) is a
  `cad.gltf` `animation()`, baked into every GLB exported from the model: parts
  translated, turned or hidden after the mechanism's pose, and the mechanism posed at
  its keys where the old clip ran it. No joint exists only to slide a part apart. Every
  old clip keeps its name and duration in one or the other; what neither can say (an
  opacity fade, a tube deformation, a chain link riding its loop, a body that leaves the
  ground) is written in each project's README as a deliberate difference.
- `@dxf` -> `@model` returning the drawing's 2D geometry, a compound of labelled
  children a layer each; `drawings/src/exports.py` writes the DXFs.

### When to use `@memo`

Rarely. The engine already replays every kernel call of any model, so `@memo` only saves
the Python cost of the memo hits a replayed function avoids (0.1-0.4 ms per hit). It
pays only where a function holds seconds of kernel work that an edit elsewhere leaves
untouched: roughly a thousand kernel calls or more. Measured here: the movement's 3
layers halve an edit (a leaf edit runs in about 4.5 s). It does not pay on small pieces:
the motorbike's 21 part markers and qdd's 7 makers saved under 0.1 s, and the movement's
19 part groups added nothing beyond its 3 layers, so those models carry none of them. A
`@memo` function must also return an assigned result (it names what its `return`
statement makes in itself, so one returning `a - b` would rename those elements), and a
marker costs a model body that is no longer one piece.

## The models

| Model | Source | What it exercises |
| --- | --- | --- |
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
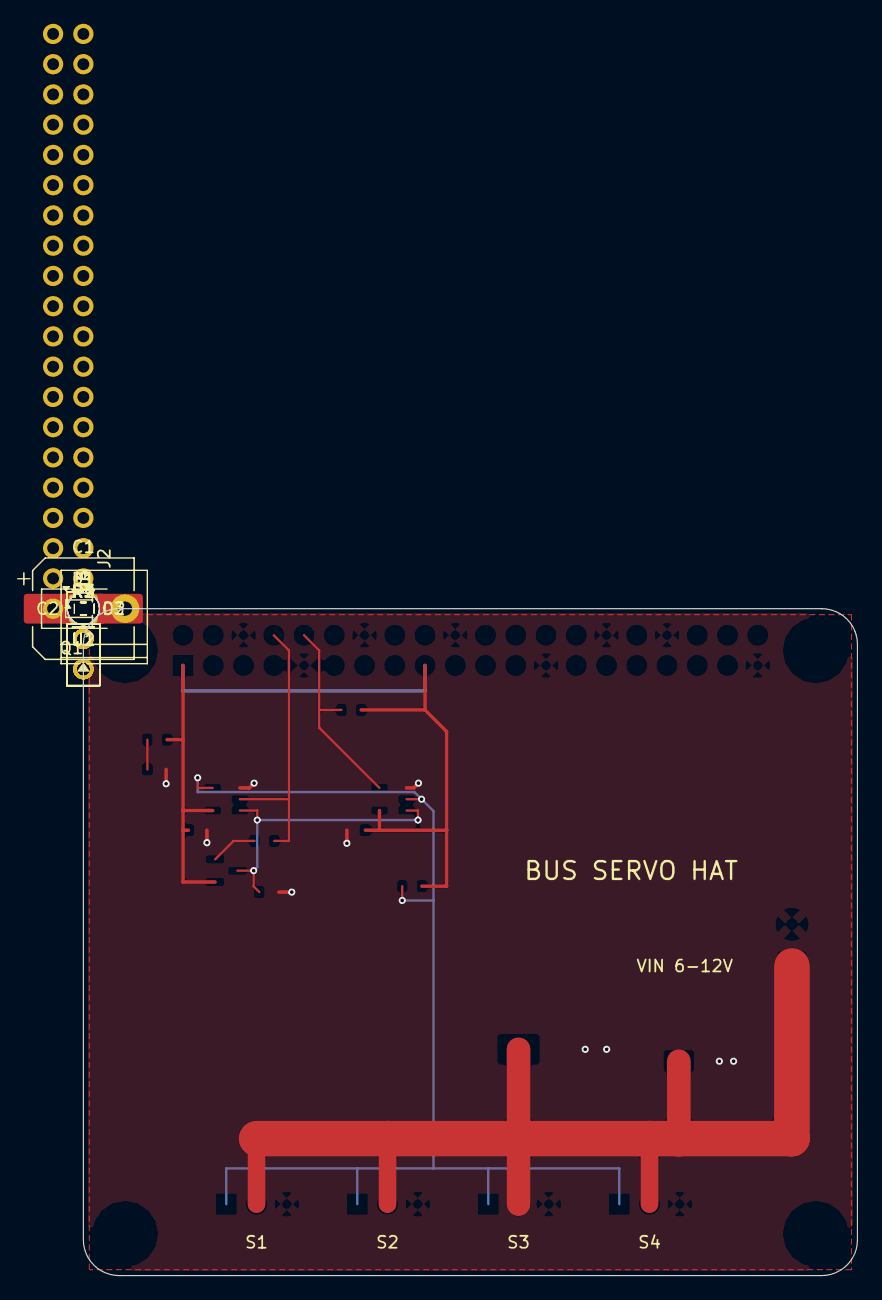
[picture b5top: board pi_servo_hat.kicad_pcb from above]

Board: 2 copper layers, 65.0 x 56.0 mm, 23 parts (1 on the bottom side), 9 nets.

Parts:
C1: 220uF 25V; CP_Elec_8x10
C2, C3: 100nF; C_0603_1608Metric
D1: SMAJ15CA; D_SMA
D2: green; LED_0603_1608Metric
H1, H2, H3, H4: M2.5; MountingHole_2.7mm_M2.5
J1: Pi GPIO; PinSocket_2x20_P2.54mm_Vertical
J2: VIN 6-12V; TerminalBlock_Phoenix_PT-1,5-2-3.5-H_1x02_P3.50mm_Horizontal
J3: servo 1; PinHeader_1x03_P2.54mm_Vertical
J4: servo 2; PinHeader_1x03_P2.54mm_Vertical
J5: servo 3; PinHeader_1x03_P2.54mm_Vertical
J6: servo 4; PinHeader_1x03_P2.54mm_Vertical
Q1: MMBT3906; SOT-23
R1, R3, R4: 10k; R_0603_1608Metric
R2: 20k; R_0603_1608Metric
R5: 1k; R_0603_1608Metric
U1: 74LVC1G126; SOT-23-5
U2: 74LVC1G125; SOT-23-5

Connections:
+3V3: C2.1, C3.1, J1.1, J1.17, Q1.2, R3.2, R4.2, R5.2, U1.5, U2.5
BASE: Q1.1, R1.1
DATA: J3.1, J4.1, J5.1, J6.1, R3.1, U1.4, U2.2
GND: C1.2, C2.2, C3.2, D1.2, D2.1, J1.6, J1.9, J1.14, J1.20, J1.25, J1.30, J1.34, J1.39, J2.2, J3.3, J4.3, J5.3, J6.3, R2.2, U1.3, U2.3
LED: D2.2, R5.1
RXD: J1.10, R4.1, U2.4
TXD: J1.8, R1.2, U1.2
TXEN: Q1.3, R2.1, U1.1, U2.1
VIN: C1.1, D1.1, J2.1, J3.2, J4.2, J5.2, J6.2

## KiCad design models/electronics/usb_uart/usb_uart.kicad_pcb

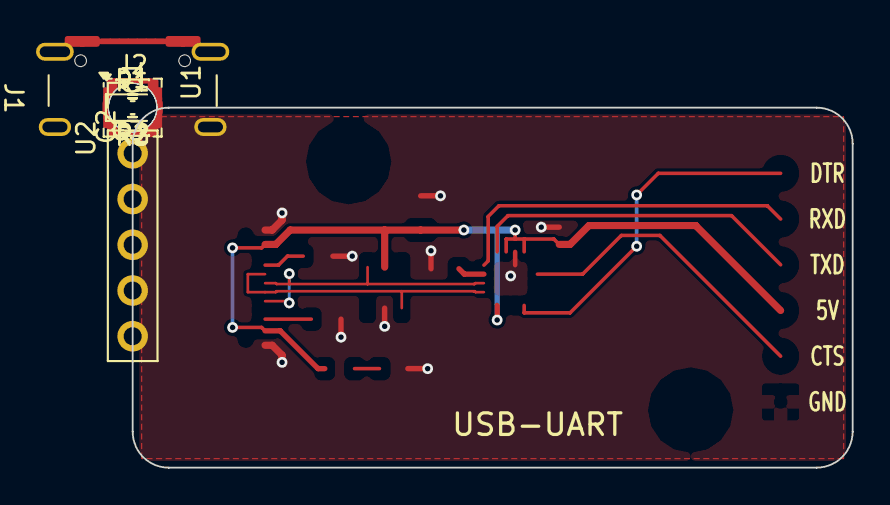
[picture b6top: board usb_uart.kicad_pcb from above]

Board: 2 copper layers, 40.0 x 20.0 mm, 13 parts (0 on the bottom side), 12 nets.

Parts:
C1: 10uF; C_0805_2012Metric
C2: 100nF; C_0402_1005Metric
C3: 1uF; C_0603_1608Metric
D1: green; LED_0603_1608Metric
H1, H2: M2.5; MountingHole_2.7mm_M2.5
J1: USB4105-GF-A; USB_C_Receptacle_GCT_USB4105-xx-A_16P_TopMnt_Horizontal
J2: FTDI; PinHeader_1x06_P2.54mm_Vertical
R1, R2: 5.1k; R_0603_1608Metric
R3: 1k; R_0603_1608Metric
U1: CH343P; WCH_QFN-16-1EP_3x3mm_P0.5mm_EP1.8x1.8mm
U2: USBLC6-2SC6; SOT-23-6

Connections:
+3V3: C3.1, U1.6
CC1: J1.A5, R1.1
CC2: J1.B5, R2.1
CTS: J2.2, U1.15
D+: J1.A6, J1.B6, U1.7, U2.6
D-: J1.A7, J1.B7, U1.8, U2.3
DTR: J2.6, U1.12
GND: C1.2, C2.2, C3.2, D1.1, J1.A1, J1.A12, J1.B1, J1.B12, J1.SH, J2.1, R1.2, R2.2, U1.2, U1.17, U2.2
LED: D1.2, R3.2
RXD: J2.5, U1.5
TXD: J2.4, U1.4
VBUS: C1.1, C2.1, J1.A4, J1.A9, J1.B4, J1.B9, J2.3, R3.1, U1.1, U1.3, U1.9, U2.5
